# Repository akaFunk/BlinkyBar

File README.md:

# BlinkyBar
The BlinkyBar is a modular LED light painting device based on the WS2812B programmable RGB LEDs. It features modules with a length of approximately 250mm, which can be attached to a host module of an arbitrary length. The host module holds a Raspberry Pi Zero W, which provides access to the device with a Wifi access point. A website running on the Raspi allows to upload an image. Once the trigger button on the host module is pressed, the image is played back one column after another. Combining this with a long time expose will paint the uploaded image into thin air.

We are currently working on the first release. Images made with an earlier version are shown below. This older version featured only 60 LEDs per meter, while the new one will have 180 LEDs per meter.

## Images
Examples of the old version:

3D rendering of the current main module:

Images of the first prototype:

## Building BlinkyBar

### Issues to be aware of
BlinkyBar is still in development and there are currently a few issues, which are important to note if you want to build it. They will be addressed in the future:
- The 1117 LDO is not working with the currently populated MLCC output capacitors. Their ESR is too low. You will hear an annoying high pitch tone and have a ~400 mVpp triangle on the output voltage. Either replace the output capacitors with Aluminium Electrolytic types, solder a 0.5 Ohm resistor in series with the capacitors, or use a different LDO (for example BL8071CLBTR33 or AP2114H-3.3TRG1). Currently we have tested only using the Aluminium Electrolytic caps which works fine.
- The modules are not able to power down automatically if the host module powers down. Please make sure to remove the batteries, otherwise they will be empty after some time. However, the battery under-voltage protection should work for both the host and the modules, so your batteries are safe.

### Parts
Additional part required for a BlinkyBar with 4 modules and the main unit, i.e., 10 module PCBs and a length of 2475 mm and 450 LEDs.
For the PCBs you will find lists in CSV format exported from KiCad in each of the PCBs output folder.

| Description | Count | 3D Model |
|---|---|---|
| U-Profile, 30x20x2x495 mm (WxHxTxL), Aluminum | 1 | main_profile |
| U-Profile, 30x20x2x495 mm (WxHxTxL), Aluminum | 4 | module_profile |
| 6x6x100 mm, Steel | 8 | module_bolt |
| 3D-printed stand for the module PCB | 15 | module_stand |
| 3D-printed power button protector | 1 | main_button_protector |
| 3D-printed main case | 1 | main_case |
| 3D-printed handle | 1 | main_handle |
| 18650 Holder | 12 | 18650_holder |
| Plate, 35x25x3 mm, Steel | 4 | module_plate |
| Main PCB holding the Raspberry Pi Zero and the user interface PCB | 1 | main_pcb |
| Main PCB adapter to combine and raise the two connector fro the module pcb within the main module | 1 | main_pcb_adapter |
| Main PCB front panel as the case cover | 1 | main_pcb_front |
| Main PCB user interface holding a few buttons and an LED | 1 | main_pcb_ui |
| Module PCB with the LEDs | 10 | module_pcb |
| M4x12 wing screw (DIN 316) | 4 | |
| M3x5 flat head screw (ISO7380) to hold the case to the profile | 2 | |
| M3x4 countersunk head screw (ISO 14581) to hold the battery holders | 24 | |
| M3 nut (ISO 4032) to hold the battery holders in the main case | 4 | |
| M3x8 flat head screw (ISO7380) to hold the main PCB in the case | 4 | |
| M3 nut (ISO 4032) to hold the main PCB in the case | 4 | |
| M3x20 flat head screw (ISO7380) to hold the front panel PCB to the case | 4 | |
| M3 nut (ISO 4032) to hold the front panel PCB to the case | 4 | |
| M3x12 flat head screw (ISO7380) to hold the stand to the profile | 28 | |
| M3x20 flat head screw (ISO7380) to hold the handle and two of the stands to the profile | 2 | |
| M3 nut (ISO 4032) to hold the stand to the profile | 30 | |
| M3x8 flat head screw (ISO7380) to hold the module PCB to the stand | 60 | |
| M3 nut (ISO 4032) to hold the module PCB to the stand | 60 | |
| M2x5 flat head screw (ISO7380) to hold the power button protector to the front panel PCB | 2 | |
| M2 nut (ISO 4032) to hold the power button protector to the front panel PCB | 2 | |
| M3x8 flat head screw (ISO7380) to hold the steel bolts to the profile | 16 | |

### Replacement parts
Some MPN in the CSV/schematics are just some random ones, for example for pin headers, which fit and were available at the time of design. Those may be replaced with similar types. A (bar far not complete) list of such parts is given below:

| Part | Description |Replacements |
|---|---|---|

# TODO/Further development
- Make everything much simpler, especially the bus topology, mechanical design, and power design
- Use smaller LEDs, for example SK6805-EC15, and increase LED density

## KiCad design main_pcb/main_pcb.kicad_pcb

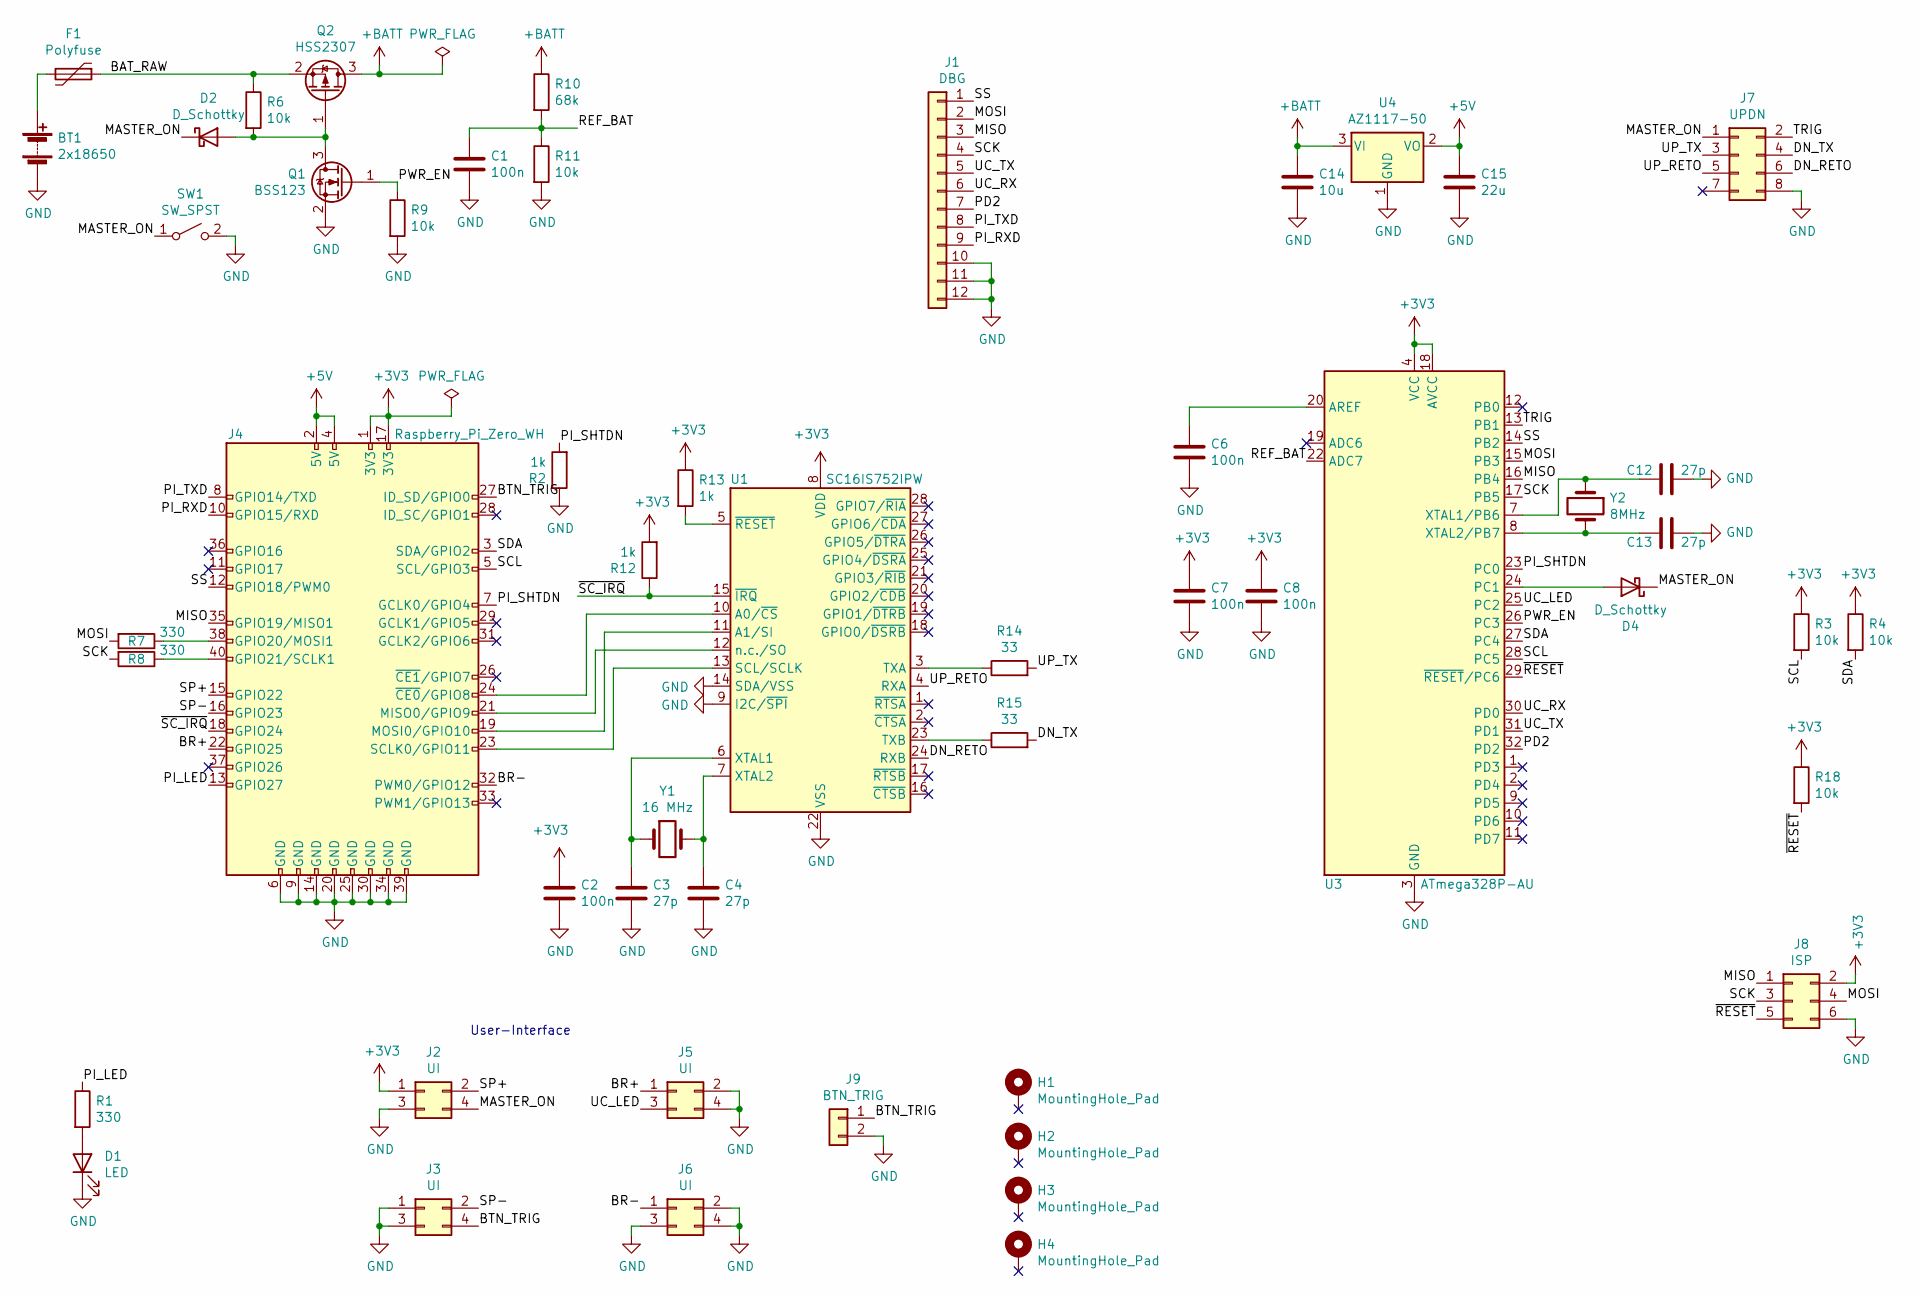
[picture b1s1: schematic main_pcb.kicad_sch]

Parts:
BT1: 2x18650; PinHeader_2x01_P2.54mm_Vertical; MPN DNP
C1, C2, C6, C7, C8: 100n; C_0603_1608Metric; MPN CC0603KRX7R0BB104
C3, C4, C12, C13: 27p; C_0603_1608Metric; MPN CC0603JRNPO9BN270
C14: 10u; C_1206_3216Metric; MPN CC1206KKX5R8BB106
C15: 22u; C_1206_3216Metric; MPN CC1206KKX5R8BB226
D1: LED; LED_0603_1608Metric; MPN LTST-C193KRKT-5A
D2, D4: D_Schottky; D_SOD-123; MPN SD103AW
F1: Polyfuse; Fuse_1812_4532Metric_Castellated; MPN BSMD1812-200-30V
H1, H2, H3, H4: MountingHole_Pad; MountingHole_3.2mm_M3_Pad; MPN DNP
J1: DBG; PinHeader_1x12_P2.54mm_Vertical; MPN KH-A2541WV-12P
J2, J3, J5, J6: UI; PinHeader_2x02_P2.54mm_Vertical; MPN C66690
J4: Raspberry_Pi_Zero_WH; RPiZero; MPN C50982
J7: UPDN; PinSocket_2x04_P2.54mm_Vertical; MPN PM254V-12-08-H85
J8: ISP; IDC-Header_2x03_P2.54mm_Vertical; MPN C11214
J9: BTN_TRIG; PinHeader_1x02_P2.54mm_Vertical; MPN DNP
Q1: BSS123; SOT-23; MPN BSS123
Q2: HSS2307; SOT-23W; MPN HSS2307
R1, R7, R8: 330; R_0603_1608Metric; MPN RC0603FR-07330RL
R2, R12, R13: 1k; R_0603_1608Metric; MPN AC0603FR-071KL
R3, R4, R6, R9, R11, R18: 10k; R_0603_1608Metric; MPN RC0603JR-0710KL
R10: 68k; R_0603_1608Metric; MPN RC0603JR-0768KL
R14, R15: 33; R_0603_1608Metric; MPN RC0603FR-0733RL
SW1: SW_SPST; SW_PUSH_6mm_H8mm; MPN K2-1102DP-J4SW-04
U1: SC16IS752IPW; TSSOP-28_4.4x9.7mm_P0.65mm; MPN SC16IS752IPW,128
U3: ATmega328P-AU; TQFP-32_7x7mm_P0.8mm; MPN ATmega328P-AU
U4: AZ1117-50; SOT-223-3_TabPin2; MPN AZ1117CH-5.0TRG1
Y1: 16 MHz; Crystal_SMD_HC49-SD; MPN C16000J119
Y2: 8MHz; Crystal_SMD_HC49-SD; MPN C16000J119

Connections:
+3V3: C2.1, C7.1, C8.1, J2.1, J4.1 (3V3), J4.17 (3V3), J8.2, R3.1, R4.1, R12.2, R13.1, R18.1, U1.8 (VDD), U3.4 (VCC), U3.6 (VCC), U3.18 (AVCC)
+5V: C15.1, J4.2 (5V), J4.4 (5V), U4.2 (VO)
+BATT: C14.1, Q2.3 (D), R10.1, U4.3 (VI)
/BAT_RAW: F1.1, Q2.2 (S), R6.1
/BR+: J4.22 (GPIO25), J5.1
/BR-: J4.32 (PWM0/GPIO12), J6.1
/BTN_TRIG: J3.4, J4.27 (ID_SD/GPIO0), J9.1
/DN_RETO: J7.6, U1.24 (RXB)
/DN_TX: J7.4, R15.2
/MASTER_ON: D2.1 (K), D4.1 (K), J2.4, J7.1, SW1.1 (A)
/MISO: J1.3, J4.35 (GPIO19/MISO1), J8.1, U3.16 (PB4)
/MOSI: J1.2, J8.4, R7.2, U3.15 (PB3)
/PD2: J1.7, U3.32 (PD2)
/PI_LED: J4.13 (GPIO27), R1.1
/PI_RXD: J1.9, J4.10 (GPIO15/RXD)
/PI_SHTDN: J4.7 (GCLK0/GPIO4), R2.2, U3.23 (PC0)
/PI_TXD: J1.8, J4.8 (GPIO14/TXD)
/PWR_EN: Q1.1 (G), R9.1, U3.26 (PC3)
/REF_BAT: C1.1, R10.2, R11.1, U3.22 (ADC7)
/SCK: J1.4, J8.3, R8.2, U3.17 (PB5)
/SCL: J4.5 (SCL/GPIO3), R3.2, U3.28 (PC5)
/SDA: J4.3 (SDA/GPIO2), R4.2, U3.27 (PC4)
/SP+: J2.2, J4.15 (GPIO22)
/SP-: J3.2, J4.16 (GPIO23)
/SS: J1.1, J4.12 (GPIO18/PWM0), U3.14 (PB2)
/TRIG: J7.2, U3.13 (PB1)
/UC_LED: J5.3, U3.25 (PC2)
/UC_RX: J1.6, U3.30 (PD0)
/UC_TX: J1.5, U3.31 (PD1)
/UP_RETO: J7.5, U1.4 (RXA)
/UP_TX: J7.3, R14.2
/~RESET: J8.5, R18.2, U3.29 (~RESET/PC6)
/~SC_IRQ: J4.18 (GPIO24), R12.1, U1.15 (~IRQ)
GND: BT1.2 (-), C1.2, C2.2, C3.2, C4.2, C6.2, C7.2, C8.2, C12.1, C13.1, C14.2, C15.2, D1.1 (K), J1.10, J1.11, J1.12, J2.3, J3.1, J3.3, J4.6 (GND), J4.9 (GND), J4.14 (GND), J4.20 (GND), J4.25 (GND), J4.30 (GND), J4.34 (GND), J4.39 (GND), J5.2, J5.4, J6.2, J6.3, J6.4, J7.8, J8.6, J9.2, Q1.2 (S), R2.1, R9.2, R11.2, SW1.2 (B), U1.9 (I2C/~SPI), U1.14 (SDA/VSS), U1.22 (VSS), U3.3 (GND), U3.5 (GND), U3.21 (GND), U4.1 (GND)
unnamed: BT1.1 (+), F1.2
unnamed: C3.1, U1.6 (XTAL1), Y1.1
unnamed: C4.1, U1.7 (XTAL2), Y1.2
unnamed: C6.1, U3.20 (AREF)
unnamed: C12.2, U3.7 (XTAL1/PB6), Y2.1
unnamed: C13.2, U3.8 (XTAL2/PB7), Y2.2
unnamed: D1.2 (A), R1.2
unnamed: D2.2 (A), Q1.3 (D), Q2.1 (G), R6.2
unnamed: D4.2 (A), U3.24 (PC1)
unnamed: J4.19 (MOSI0/GPIO10), U1.11 (A1/SI)
unnamed: J4.21 (MISO0/GPIO9), U1.12 (n.c./SO)
unnamed: J4.23 (SCLK0/GPIO11), U1.13 (SCL/SCLK)
unnamed: J4.24 (~CE0/GPIO8), U1.10 (A0/~CS)
unnamed: J4.38 (GPIO20/MOSI1), R7.1
unnamed: J4.40 (GPIO21/SCLK1), R8.1
unnamed: R13.2, U1.5 (~RESET)
unnamed: R14.1, U1.3 (TXA)
unnamed: R15.1, U1.23 (TXB)

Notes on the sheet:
User-Interface

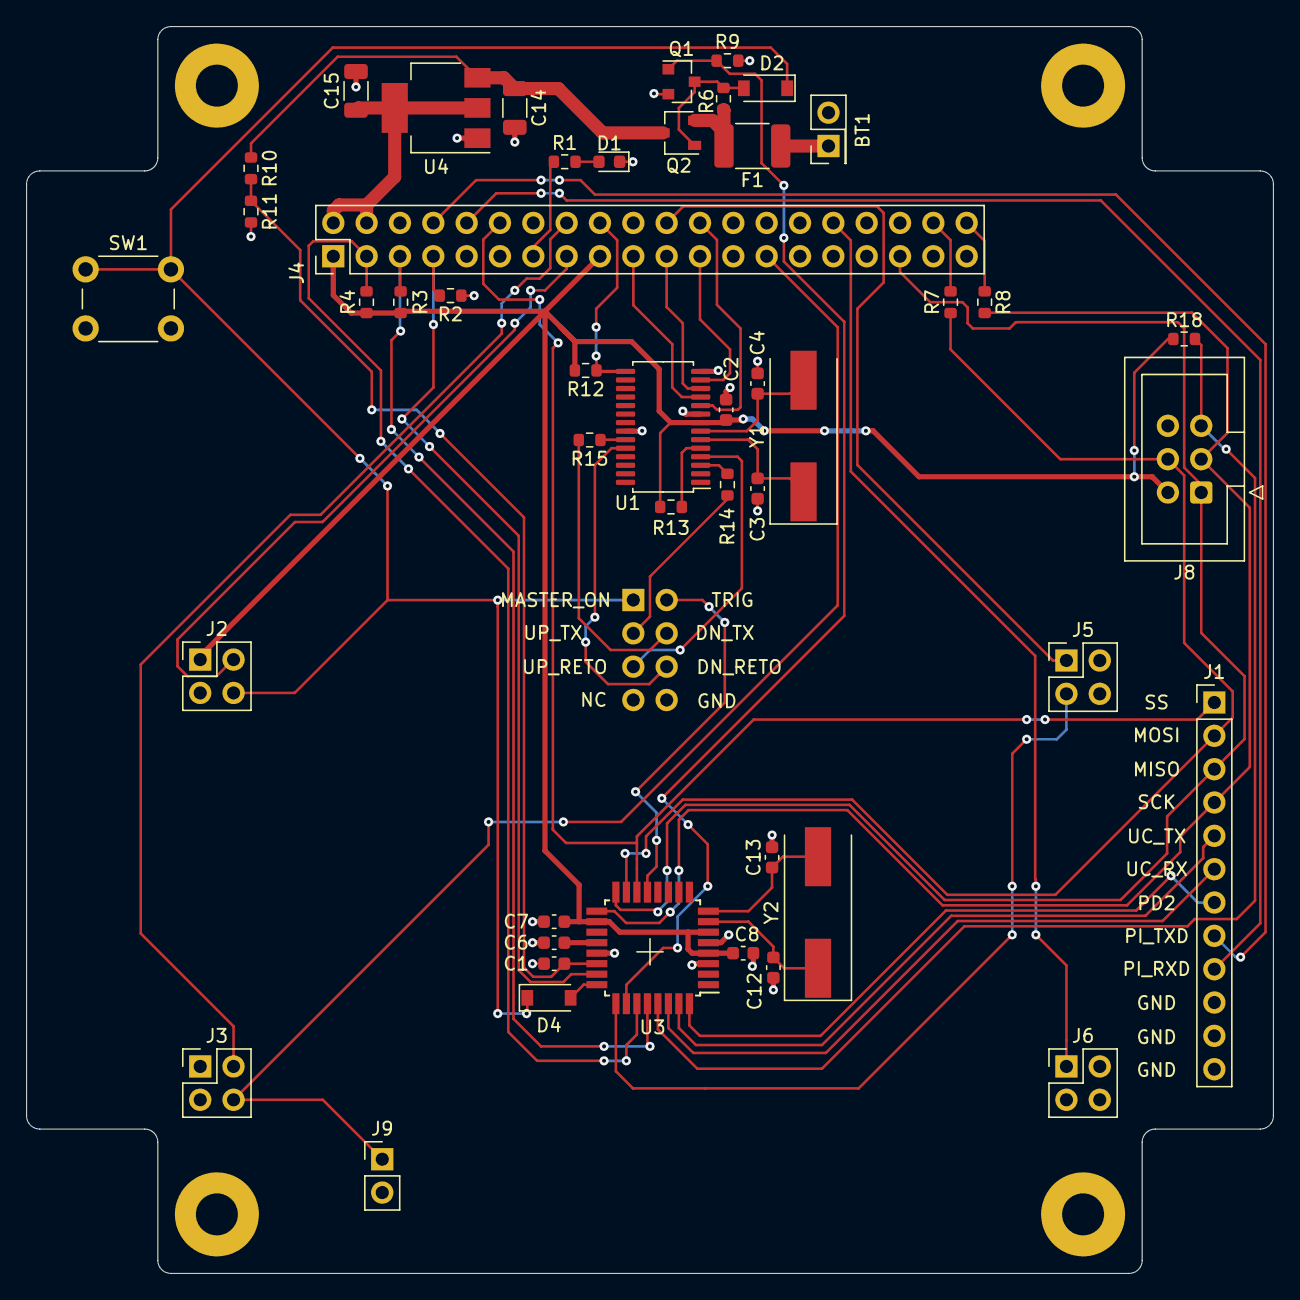
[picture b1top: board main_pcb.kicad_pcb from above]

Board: 2 copper layers, 95.0 x 95.0 mm, 52 parts (1 on the bottom side), 52 nets.

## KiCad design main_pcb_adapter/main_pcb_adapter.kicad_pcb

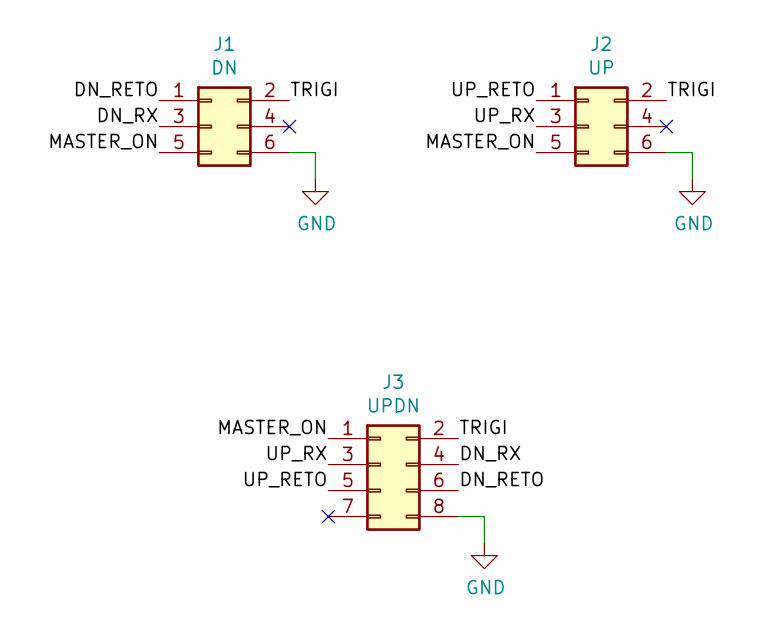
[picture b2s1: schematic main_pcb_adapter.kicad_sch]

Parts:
J1: DN; PinSocket_2x03_P2.54mm_Vertical; MPN DS1023-2*3SF11
J2: UP; PinSocket_2x03_P2.54mm_Vertical; MPN DS1023-2*3SF11
J3: UPDN; PinHeader_2x04_P2.54mm_Vertical; MPN B-2100S08P-B110

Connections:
/DN_RETO: J1.1, J3.6
/DN_RX: J1.3, J3.4
/MASTER_ON: J1.5, J2.5, J3.1
/TRIGI: J1.2, J2.2, J3.2
/UP_RETO: J2.1, J3.5
/UP_RX: J2.3, J3.3
GND: J1.6, J2.6, J3.8

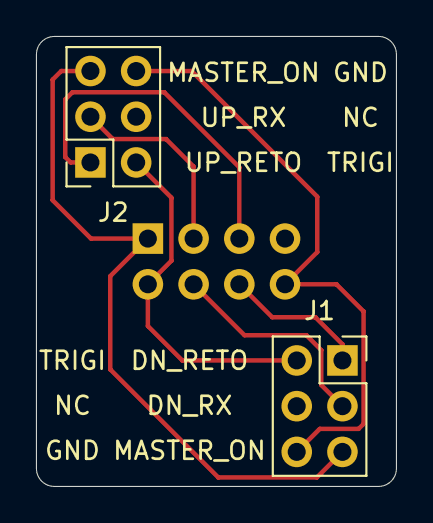
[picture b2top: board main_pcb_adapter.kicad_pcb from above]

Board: 2 copper layers, 20.0 x 25.0 mm, 3 parts (1 on the bottom side), 7 nets.

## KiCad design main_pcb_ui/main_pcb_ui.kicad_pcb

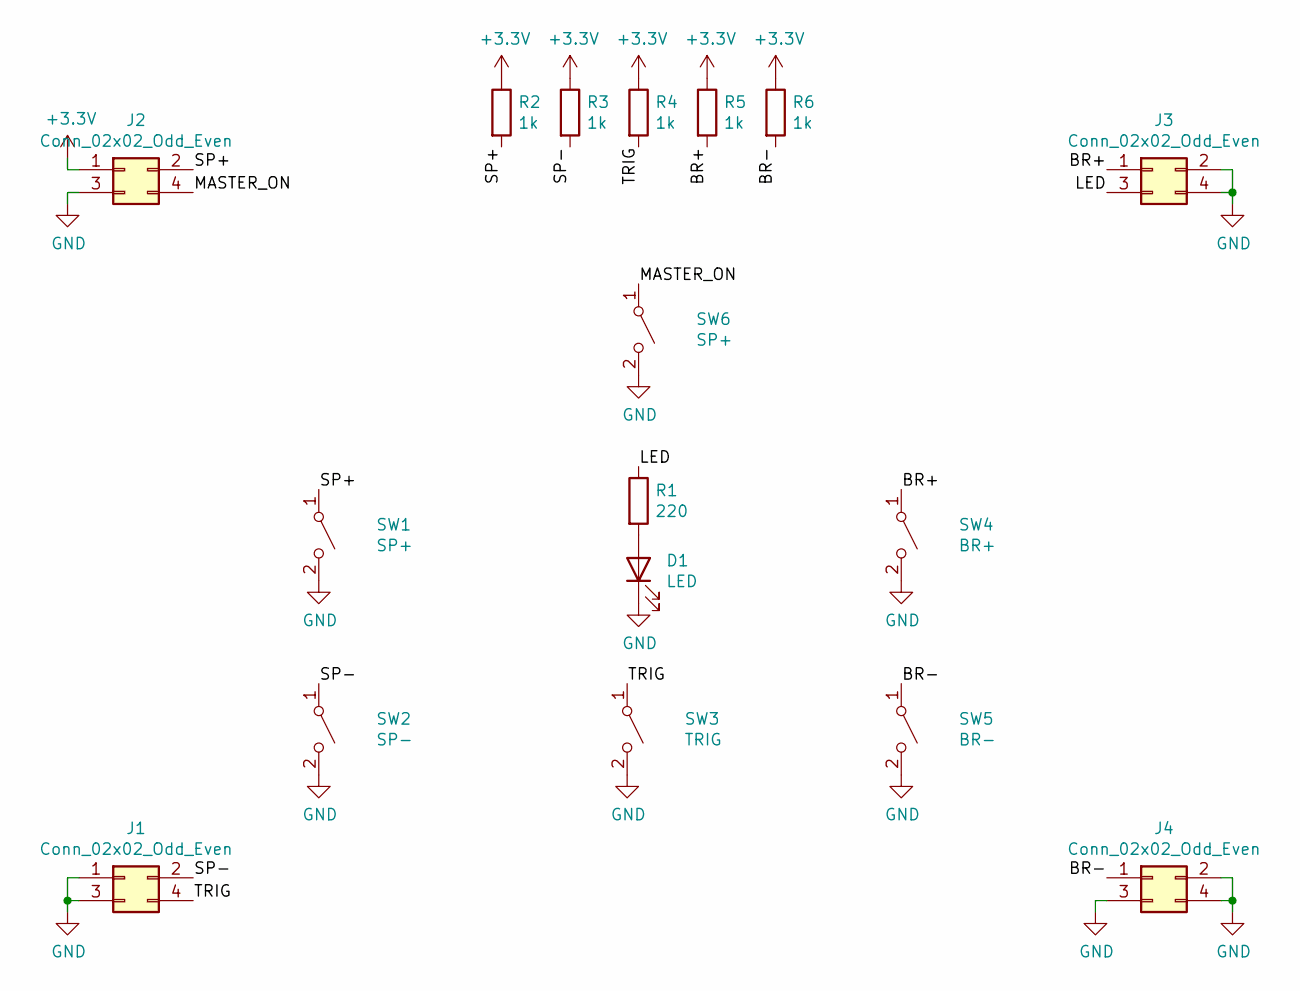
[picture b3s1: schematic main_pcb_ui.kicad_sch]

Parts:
D1: LED; LED_D3.0mm; MPN HL-304S9AD
J1, J3, J4: Conn_02x02_Odd_Even; PinSocket_2x02_P2.54mm_Vertical; MPN C66690
J2: Conn_02x02_Odd_Even; PinSocket_2x02_P2.54mm_Vertical; MPN DS1023-2*2SF11
R1: 220; R_0603_1608Metric; MPN CR0603FA2200G
R2, R3, R4, R5, R6: 1k; R_0603_1608Metric; MPN RC0603JR-071KL
SW1, SW6: SP+; SW_PUSH_6mm_H8mm; MPN TS4570CJ
SW2: SP-; SW_PUSH_6mm_H8mm; MPN TS4570CJ
SW3: TRIG; SW_PUSH_6mm_H8mm; MPN TS4570CJ
SW4: BR+; SW_PUSH_6mm_H8mm; MPN TS4570CJ
SW5: BR-; SW_PUSH_6mm_H8mm; MPN TS4570CJ

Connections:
+3V3: J2.1, R2.1, R3.1, R4.1, R5.1, R6.1
/BR+: J3.1, R5.2, SW4.1 (A)
/BR-: J4.1, R6.2, SW5.1 (A)
/LED: J3.3, R1.1
/MASTER_ON: J2.4, SW6.1 (A)
/SP+: J2.2, R2.2, SW1.1 (A)
/SP-: J1.2, R3.2, SW2.1 (A)
/TRIG: J1.4, R4.2, SW3.1 (A)
GND: D1.1 (K), J1.1, J1.3, J2.3, J3.2, J3.4, J4.2, J4.3, J4.4, SW1.2 (B), SW2.2 (B), SW3.2 (B), SW4.2 (B), SW5.2 (B), SW6.2 (B)
unnamed: D1.2 (A), R1.2

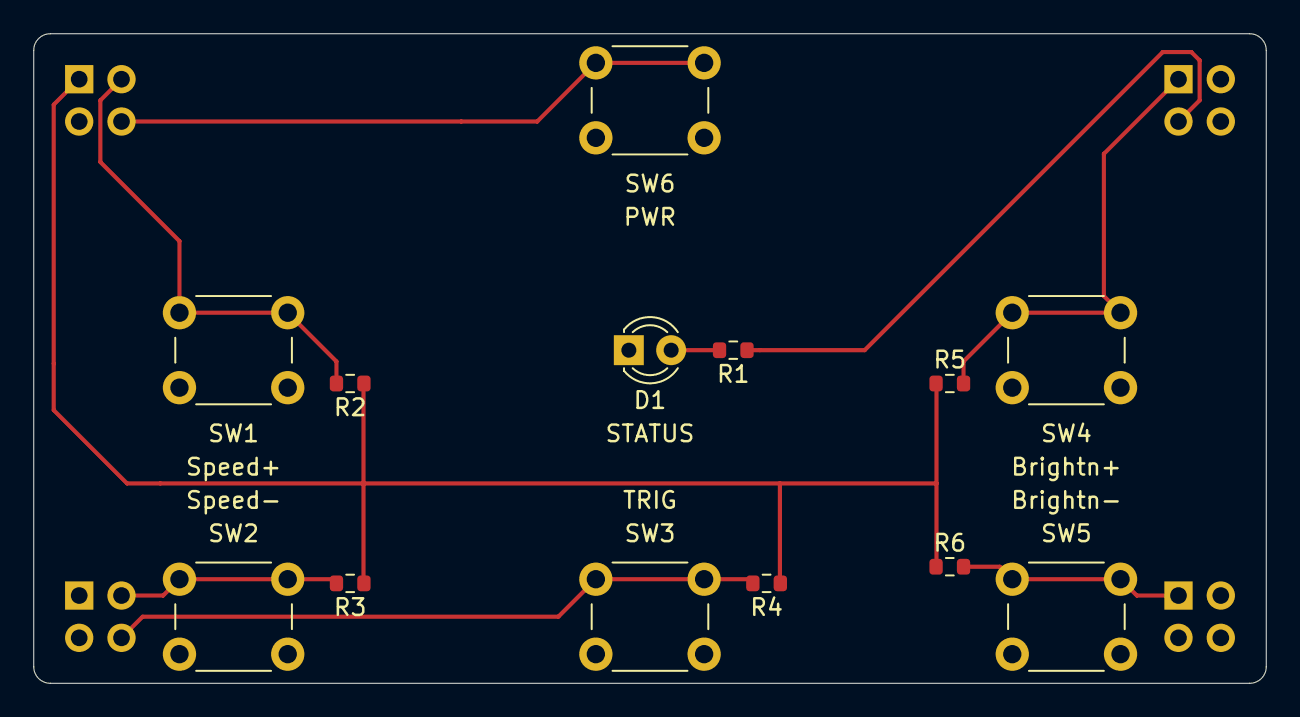
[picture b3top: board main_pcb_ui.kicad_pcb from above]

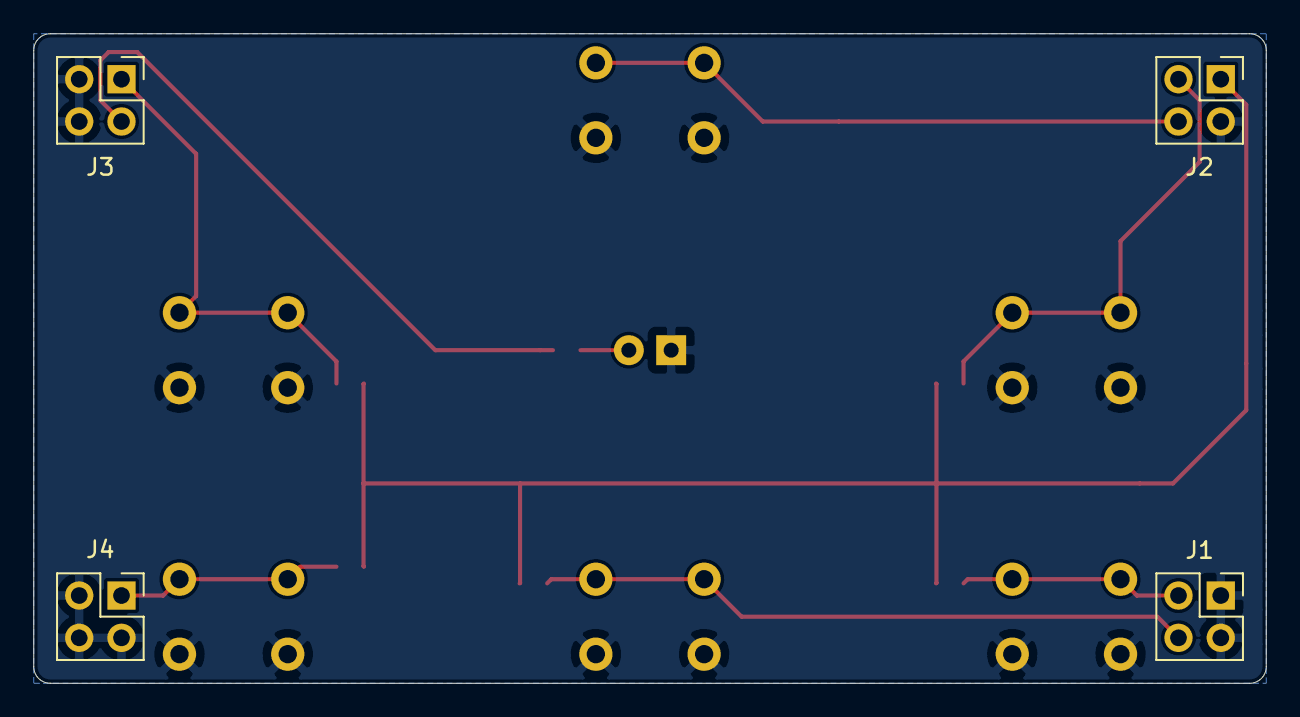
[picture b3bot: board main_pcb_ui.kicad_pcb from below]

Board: 2 copper layers, 74.0 x 39.0 mm, 17 parts (4 on the bottom side), 10 nets.

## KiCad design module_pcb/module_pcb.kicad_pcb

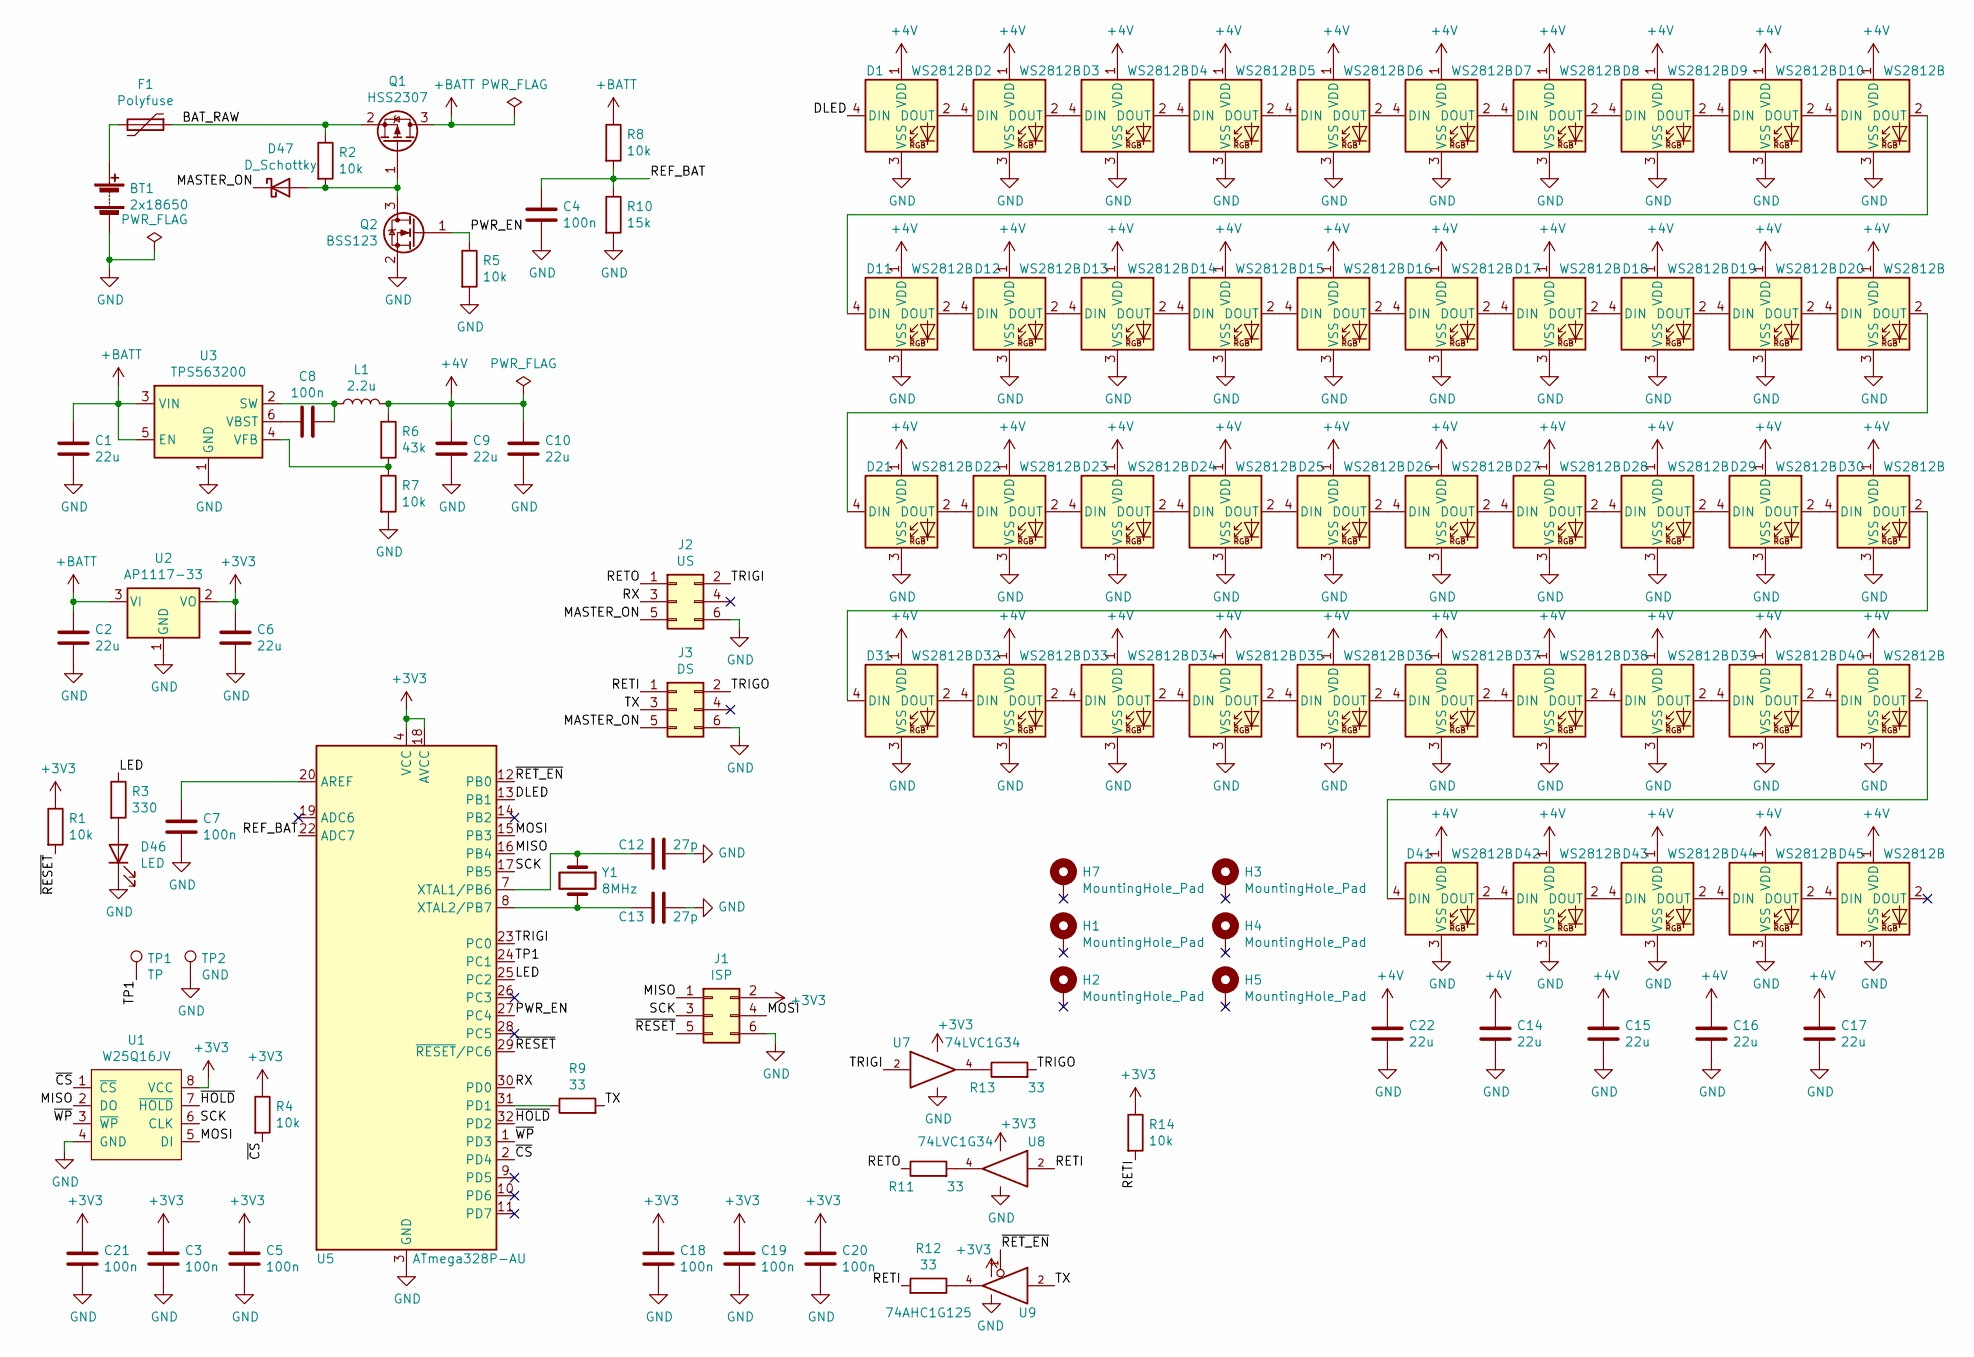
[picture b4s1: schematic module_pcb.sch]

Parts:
BT1: 2x18650; PinHeader_2x01_P2.54mm_Vertical; MPN DNP
C1, C2, C6, C9, C10, C14, C15, C16, C17, C22: 22u; C_1206_3216Metric; MPN CC1206KKX5R8BB226
C3, C4, C5, C7, C8, C18, C19, C20, C21: 100n; C_0603_1608Metric; MPN CC0603KRX7R0BB104
C12, C13: 27p; C_0603_1608Metric; MPN CC0603JRNPO9BN270
D1, D2, D3, D4, D5, D6, D7, D8, D9, D10, D11, D12, D13, D14, D15, D16, D17, D18, D19, D20, D21, D22, D23, D24, D25, D26, D27, D28, D29, D30, D31, D32, D33, D34, D35, D36, D37, D38, D39, D40, D41, D42, D43, D44, D45: WS2812B; LED_WS2812B_PLCC4_5.0x5.0mm_P3.2mm; MPN WS2812B
D46: LED; LED_0603_1608Metric; MPN LTST-C193KRKT-5A
D47: D_Schottky; D_SOD-123; MPN SD103AW
F1: Polyfuse; Fuse_1812_4532Metric_Castellated; MPN BSMD1812-200-30V
H1, H2, H3, H4, H5, H7: MountingHole_Pad; MountingHole_3.2mm_M3_Pad; MPN DNP
J1: ISP; PinHeader_2x03_P2.54mm_Vertical; MPN 210-72-03GB01
J2: US; PinHeader_2x03_P2.54mm_Horizontal; MPN PZ254R-12-6P
J3: DS; PinSocket_2x03_P2.54mm_Horizontal; MPN C576162
L1: 2.2u; L_Abracon_ASPI-0630LR; MPN MJC-0603T-2R2-M
Q1: HSS2307; SOT-23W; MPN HSS2307
Q2: BSS123; SOT-23; MPN BSS123
R1, R2, R4, R5, R7, R8, R14: 10k; R_0603_1608Metric; MPN RC0603FR-0710KL
R3: 330; R_0603_1608Metric; MPN RC0603FR-07330RL
R6: 43k; R_0603_1608Metric; MPN RC0603FR-0743KL
R9, R11, R12, R13: 33; R_0603_1608Metric; MPN RC0603FR-0733RL
R10: 15k; R_0603_1608Metric; MPN RC0603FR-0715KL
TP1: TP; TestPoint_Pad_D1.5mm; MPN DNP
TP2: GND; TestPoint_Pad_D1.5mm; MPN DNP
U1: W25Q16JV; SOIC-8_5.23x5.23mm_P1.27mm; MPN W25Q16JVSSIQ
U2: AP1117-33; SOT-223-3_TabPin2; MPN AP1117E33G-13
U3: TPS563200; SOT-23-6; MPN TPS563200DDCR
U5: ATmega328P-AU; TQFP-32_7x7mm_P0.8mm; MPN ATmega328P-AU
U7, U8: 74LVC1G34; SOT-353_SC-70-5; MPN 74LVC1G34GW,125
U9: 74AHC1G125; SOT-23-5; MPN SN74AHC1G125DBVR
Y1: 8MHz; Crystal_SMD_HC49-SD; MPN C08000J060

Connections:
+3V3: C3.1, C5.1, C6.1, C18.1, C19.1, C20.1, C21.1, J1.2, R1.1, R4.1, R14.1, U1.8 (VCC), U2.2 (VO), U5.4 (VCC), U5.6 (VCC), U5.18 (AVCC), U7.5 (VCC), U8.5 (VCC), U9.5 (VCC)
+4V: C9.1, C10.1, C14.1, C15.1, C16.1, C17.1, C22.1, D1.1 (VDD), D2.1 (VDD), D3.1 (VDD), D4.1 (VDD), D5.1 (VDD), D6.1 (VDD), D7.1 (VDD), D8.1 (VDD), D9.1 (VDD), D10.1 (VDD), D11.1 (VDD), D12.1 (VDD), D13.1 (VDD), D14.1 (VDD), D15.1 (VDD), D16.1 (VDD), D17.1 (VDD), D18.1 (VDD), D19.1 (VDD), D20.1 (VDD), D21.1 (VDD), D22.1 (VDD), D23.1 (VDD), D24.1 (VDD), D25.1 (VDD), D26.1 (VDD), D27.1 (VDD), D28.1 (VDD), D29.1 (VDD), D30.1 (VDD), D31.1 (VDD), D32.1 (VDD), D33.1 (VDD), D34.1 (VDD), D35.1 (VDD), D36.1 (VDD), D37.1 (VDD), D38.1 (VDD), D39.1 (VDD), D40.1 (VDD), D41.1 (VDD), D42.1 (VDD), D43.1 (VDD), D44.1 (VDD), D45.1 (VDD), L1.2, R6.1
+BATT: C1.1, C2.1, Q1.3 (D), R8.1, U2.3 (VI), U3.3 (VIN), U3.5 (EN)
/BAT_RAW: F1.1, Q1.2 (S), R2.1
/DLED: D1.4 (DIN), U5.13 (PB1)
/LED: R3.1, U5.25 (PC2)
/MASTER_ON: D47.1 (K), J2.5, J3.5
/MISO: J1.1, U1.2 (DO), U5.16 (PB4)
/MOSI: J1.4, U1.5 (DI), U5.15 (PB3)
/PWR_EN: Q2.1 (G), R5.1, U5.27 (PC4)
/REF_BAT: C4.1, R8.2, R10.1, U5.22 (ADC7)
/RETI: J3.1, R12.2, R14.2, U8.2
/RETO: J2.1, R11.1
/RX: J2.3, U5.30 (PD0)
/SCK: J1.3, U1.6 (CLK), U5.17 (PB5)
/TP1: TP1.1, U5.24 (PC1)
/TRIGI: J2.2, U5.23 (PC0), U7.2
/TRIGO: J3.2, R13.2
/TX: J3.3, R9.2, U9.2
/~CS: R4.2, U1.1 (~CS), U5.2 (PD4)
/~HOLD: U1.7 (~HOLD), U5.32 (PD2)
/~RESET: J1.5, R1.2, U5.29 (~RESET~/PC6)
/~RET_EN: U5.12 (PB0), U9.1
/~WP: U1.3 (~WP), U5.1 (PD3)
GND: BT1.2 (-), C1.2, C2.2, C3.2, C4.2, C5.2, C6.2, C7.2, C9.2, C10.2, C12.1, C13.1, C14.2, C15.2, C16.2, C17.2, C18.2, C19.2, C20.2, C21.2, C22.2, D1.3 (VSS), D2.3 (VSS), D3.3 (VSS), D4.3 (VSS), D5.3 (VSS), D6.3 (VSS), D7.3 (VSS), D8.3 (VSS), D9.3 (VSS), D10.3 (VSS), D11.3 (VSS), D12.3 (VSS), D13.3 (VSS), D14.3 (VSS), D15.3 (VSS), D16.3 (VSS), D17.3 (VSS), D18.3 (VSS), D19.3 (VSS), D20.3 (VSS), D21.3 (VSS), D22.3 (VSS), D23.3 (VSS), D24.3 (VSS), D25.3 (VSS), D26.3 (VSS), D27.3 (VSS), D28.3 (VSS), D29.3 (VSS), D30.3 (VSS), D31.3 (VSS), D32.3 (VSS), D33.3 (VSS), D34.3 (VSS), D35.3 (VSS), D36.3 (VSS), D37.3 (VSS), D38.3 (VSS), D39.3 (VSS), D40.3 (VSS), D41.3 (VSS), D42.3 (VSS), D43.3 (VSS), D44.3 (VSS), D45.3 (VSS), D46.1 (K), J1.6, J2.6, J3.6, Q2.2 (S), R5.2, R7.2, R10.2, TP2.1, U1.4 (GND), U2.1 (GND), U3.1 (GND), U5.3 (GND), U5.5 (GND), U5.21 (GND), U7.3 (GND), U8.3 (GND), U9.3 (GND)
unnamed: BT1.1 (+), F1.2
unnamed: C7.1, U5.20 (AREF)
unnamed: C8.1, U3.6 (VBST)
unnamed: C8.2, L1.1, U3.2 (SW)
unnamed: C12.2, U5.7 (XTAL1/PB6), Y1.1
unnamed: C13.2, U5.8 (XTAL2/PB7), Y1.2
unnamed: D1.2 (DOUT), D2.4 (DIN)
unnamed: D2.2 (DOUT), D3.4 (DIN)
unnamed: D3.2 (DOUT), D4.4 (DIN)
unnamed: D4.2 (DOUT), D5.4 (DIN)
unnamed: D5.2 (DOUT), D6.4 (DIN)
unnamed: D6.2 (DOUT), D7.4 (DIN)
unnamed: D7.2 (DOUT), D8.4 (DIN)
unnamed: D8.2 (DOUT), D9.4 (DIN)
unnamed: D10.2 (DOUT), D11.4 (DIN)
unnamed: D9.2 (DOUT), D10.4 (DIN)
unnamed: D11.2 (DOUT), D12.4 (DIN)
unnamed: D12.2 (DOUT), D13.4 (DIN)
unnamed: D13.2 (DOUT), D14.4 (DIN)
unnamed: D14.2 (DOUT), D15.4 (DIN)
unnamed: D15.2 (DOUT), D16.4 (DIN)
unnamed: D16.2 (DOUT), D17.4 (DIN)
unnamed: D17.2 (DOUT), D18.4 (DIN)
unnamed: D18.2 (DOUT), D19.4 (DIN)
unnamed: D19.2 (DOUT), D20.4 (DIN)
unnamed: D20.2 (DOUT), D21.4 (DIN)
unnamed: D21.2 (DOUT), D22.4 (DIN)
unnamed: D22.2 (DOUT), D23.4 (DIN)
unnamed: D23.2 (DOUT), D24.4 (DIN)
unnamed: D24.2 (DOUT), D25.4 (DIN)
unnamed: D25.2 (DOUT), D26.4 (DIN)
unnamed: D26.2 (DOUT), D27.4 (DIN)
unnamed: D27.2 (DOUT), D28.4 (DIN)
unnamed: D28.2 (DOUT), D29.4 (DIN)
unnamed: D29.2 (DOUT), D30.4 (DIN)
unnamed: D30.2 (DOUT), D31.4 (DIN)
unnamed: D31.2 (DOUT), D32.4 (DIN)
unnamed: D32.2 (DOUT), D33.4 (DIN)
unnamed: D33.2 (DOUT), D34.4 (DIN)
unnamed: D34.2 (DOUT), D35.4 (DIN)
unnamed: D35.2 (DOUT), D36.4 (DIN)
unnamed: D36.2 (DOUT), D37.4 (DIN)
unnamed: D37.2 (DOUT), D38.4 (DIN)
unnamed: D38.2 (DOUT), D39.4 (DIN)
unnamed: D39.2 (DOUT), D40.4 (DIN)
unnamed: D40.2 (DOUT), D41.4 (DIN)
unnamed: D41.2 (DOUT), D42.4 (DIN)
unnamed: D42.2 (DOUT), D43.4 (DIN)
unnamed: D43.2 (DOUT), D44.4 (DIN)
unnamed: D44.2 (DOUT), D45.4 (DIN)
unnamed: D46.2 (A), R3.2
unnamed: D47.2 (A), Q1.1 (G), Q2.3 (D), R2.2
unnamed: R6.2, R7.1, U3.4 (VFB)
unnamed: R9.1, U5.31 (PD1)
unnamed: R11.2, U8.4
unnamed: R12.1, U9.4
unnamed: R13.1, U7.4

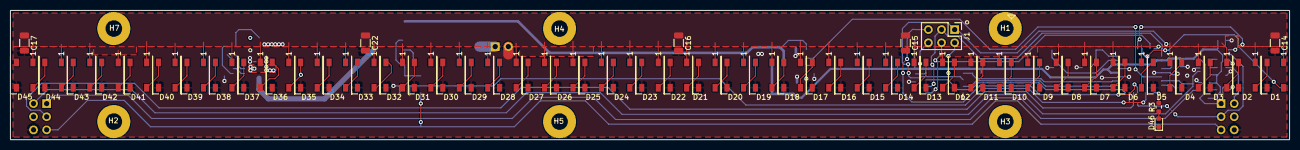
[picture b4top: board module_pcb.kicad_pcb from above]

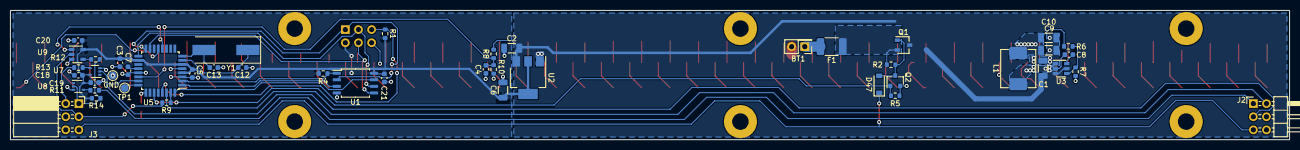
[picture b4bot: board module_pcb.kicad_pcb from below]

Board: 2 copper layers, 247.5 x 25.0 mm, 106 parts (47 on the bottom side), 82 nets.

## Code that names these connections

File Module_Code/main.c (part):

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#include <string.h>

#define RET_EN_DDR                  DDRB
#define RET_EN_PORT                 PORTB
#define RET_EN_PIN                  0

#define PWR_EN_DDR                  DDRC
#define PWR_EN_PORT                 PORTC
#define PWR_EN_PIN                  4

#define TRIG_DDR                    DDRC  // PCINT8
#define TRIG_PORT                   PORTC
#define TRIG_PIN                    0

#define LED_DDR                     DDRC
#define LED_PORT                    PORTC
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#define MESSAGE_TYPE_IMG_NEW        0x40    // Start storing a new image, len=0
#define MESSAGE_TYPE_IMG_APP        0x41    // Next image data block, len=1..256, must be 256 for all messages except the last one for an image
#define MESSAGE_TYPE_PREP           0x50    // All data transmitted to modules, prepare for trigger, len=0
#define MESSAGE_TYPE_TRIG           0x51    // Trigger a column - just for debug purposes, normal operation though TRIGI signal interrupt
#define MESSAGE_TYPE_ACK            0xf0    // ACK last message (also used as pong), len=0
#define MESSAGE_TYPE_NACK           0xf1    // NACK last message, len=0

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int main()
{
    // Init GPIOs
    RET_EN_PORT |= (1<<RET_EN_PIN);  // Disable return path by default
    RET_EN_DDR |= (1<<RET_EN_PIN);
    PWR_EN_PORT &= (1<<PWR_EN_PIN);  // Disable own power supply by default
    PWR_EN_DDR |= (1<<PWR_EN_PIN);
    LED_DDR |= (1<<LED_PIN);

    // Before we do anything, we wait 2 seconds, then turn on the power supply for ourself
    _delay_ms(200);  // TODO: Reset to ~2000
    PWR_EN_PORT |= (1<<PWR_EN_PIN);

    ws2812b_init();
    uart_init();
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    display_status(0);

    // Set up trigger interrupt
    TRIG_DDR &= ~(1<<TRIG_PIN);
    TRIG_PORT |= (1<<TRIG_PIN); // Enable pull-up
    PCICR |= (1<<PCIE1);
    PCMSK1 |= (1<<TRIG_PIN);

    // Test flash
    //debug_flash()
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        if(msg->len != 0)
            return transmit_response(0);
        // Disable the RET* transmitter, we don't know how many modules are after us
        RET_EN_PORT |= (1<<RET_EN_PIN);
        return;  // don't send an ACK, no one will get it anyways
    case MESSAGE_TYPE_RET_ENABLE:
        if(msg->len != 0)
            return transmit_response(0);
        // Enable the RET* transmitter
        RET_EN_PORT &= ~(1<<RET_EN_PIN);
        break;
    case MESSAGE_TYPE_PING:
        // Fall through to send ACK
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{
    // DEBUG - Test flash image write and automatic erase
    uint8_t data[256];
    RET_EN_PORT &= ~(1<<RET_EN_PIN);  // Enable return path for debug
    _delay_ms(200);  // wait a moment for the uart line to stabilize
    flash_sm_init();
    flash_sm_print_state();
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{
    uint8_t data[256];
    // DEBUG - Test flash block write and read process
    RET_EN_PORT &= ~(1<<RET_EN_PIN);  // Enable return path for debug
    uart_putcc("\r\nStarted\r\n");
    flash_chip_erase();
    uart_putcc("Chip erased\r\n");
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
